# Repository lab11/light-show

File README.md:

Light Show
==========

This repository contains material to use one of the pseudo-addressable LED light
strips (based on the WS2801) with a Raspberry Pi.

Hardware
--------

In the hardware folder is a board design for a simple Raspberry Pi shield
that makes it easy to connect the lights to the RPi and an external power
supply.

Kernel Module
-------------

The kernel module is a simple driver for the lights that exports a character
device interface that an application can write to.

    make ARCH=arm CROSS_COMPILE=arm-linux-gnueabi-

C Code
------

The C code is a little bit of a hodgepodge of different applications that
run the lights with different applications.

    sudo apt-get install libjson0-dev

Remote Access
-------------

The app 'remote' in `c/apps/remote.c` provides network-controllable access for
the lights. Control of the strand is retained by the remote application for up
to 60 seconds, you may give up your quanta earlier by closing the connection. To
ensure responsiveness, a remote application must send a message every 3 seconds
or it will be dropped.

`remote/light_show.py` provides a basic python class and example for controlling
the lights over the remote interface.

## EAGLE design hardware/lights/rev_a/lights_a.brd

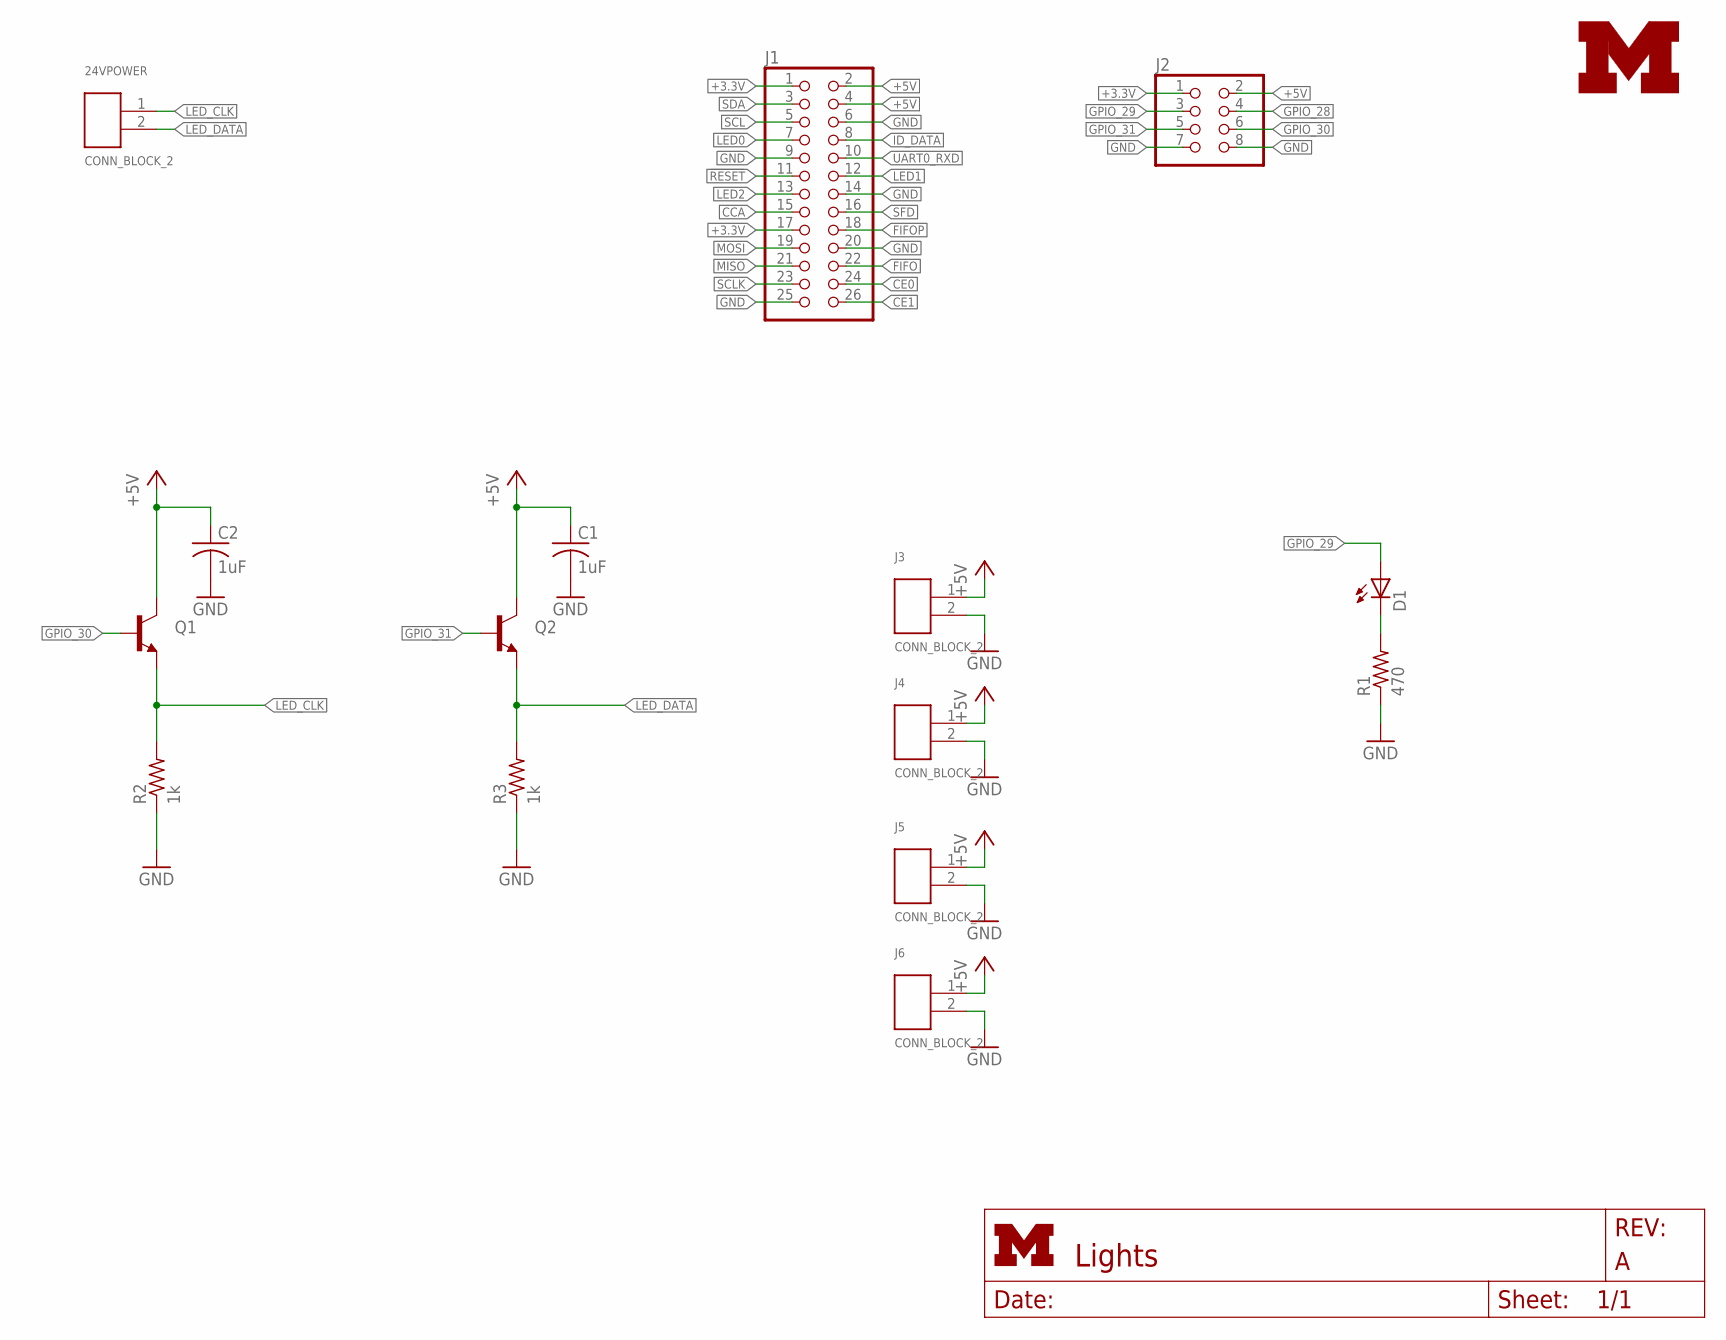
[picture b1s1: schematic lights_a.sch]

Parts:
24VPOWER: CONN_BLOCK_2
C1, C2: 1uF; C0603
D1: LED0603; LED-0603; DIGIKEY 160-1834-1-ND
J1: PINHD-2X13; 2X13; DIGIKEY SAM1204-13-ND
J2: PINHD-2X4; 2X04
J3, J4, J5, J6: CONN_BLOCK_2
Q1, Q2: TRANSISTOR_NPNSOT23; SOT23
R1: 470; R0603
R2, R3: 1k; R0603
U$1: UMICH_SOLID_SMALL; UMICH_SOLID_75MIL

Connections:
!RESET: J1.11
+3.3V: J1.1, J1.17, J2.1
+5V: C1.1, C2.1, J1.2, J1.4, J2.2, J3.1, J4.1, J5.1, J6.1, Q1.3 (C), Q2.3 (C)
CCA: J1.15
CE0: J1.24
CE1: J1.26
FIFO: J1.22
FIFOP: J1.18
GND: C1.2, C2.2, J1.6, J1.9, J1.14, J1.20, J1.25, J2.7, J2.8, J3.2, J4.2, J5.2, J6.2, R1.1, R2.1, R3.1
GPIO_28: J2.4
GPIO_29: D1.A, J2.3
GPIO_30: J2.6, Q1.1 (B)
GPIO_31: J2.5, Q2.1 (B)
ID_DATA: J1.8
LED0: J1.7
LED1: J1.12
LED2: J1.13
LED_CLK: 24VPOWER.1, Q1.2 (E), R2.2
LED_DATA: 24VPOWER.2, Q2.2 (E), R3.2
MISO: J1.21
MOSI: J1.19
unnamed: D1.C, R1.2
SCL: J1.5
SCLK: J1.23
SDA: J1.3
SFD: J1.16
UART0_RXD: J1.10

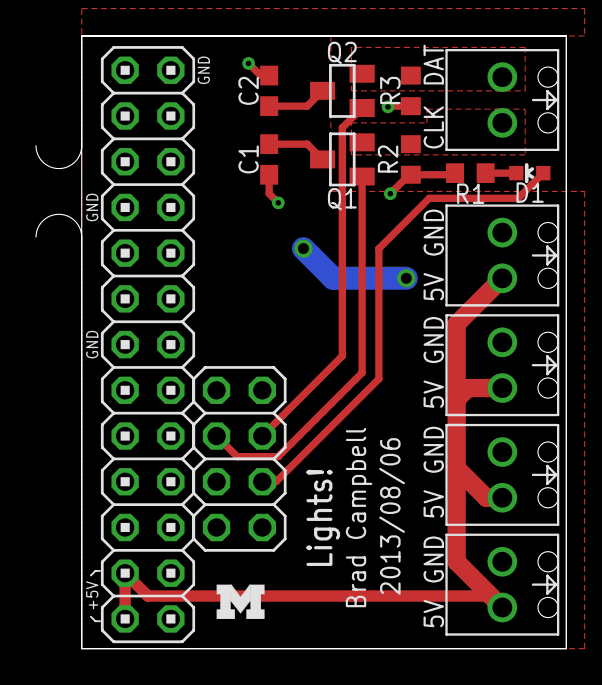
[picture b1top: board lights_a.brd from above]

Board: 2 copper layers, 29.5 x 34.0 mm, 16 parts (0 on the bottom side), 9 nets.

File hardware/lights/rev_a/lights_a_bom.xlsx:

Qty | Value | Device | Package | Parts | Description | DIGIKEY
2 | 1uF | C-USC0603 | C0603 | C1, C2 | CAPACITOR, American symbol
1 |  | LED0603 | LED-0603 | D1 | LEDs | 160-1834-1-ND
1 |  | PINHD-2X13 | 2X13 | J1 | PIN HEADER | SAM1204-13-ND
1 |  | PINHD-2X4 | 2X04 | J2 | PIN HEADER | SAM1204-04-ND
5 | CONN_BLOCK_2 | CONN_BLOCK_2 | CONN_BLOCK_2 | J3, J4, J5, J6 | 2x 0.100 in screw terminal block | 277-1273-ND
2 |  | TRANSISTOR_PFETSOT23 | SOT23 | Q1, Q2 | Transistor PFET | ZXMP2120FFCT-ND
1 | 470 | R-US_R0603 | R0603 | R1 | RESISTOR, American symbol
2 | 1k | R-US_R0603 | R0603 | R2, R3 | RESISTOR, American symbol

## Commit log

2013-06-29 First test pass on sparkfuns code
2013-06-29 gitignore
2013-06-29 random now walks down some colors
2013-06-29 new tracer app
2013-07-02 added stream receiver to tracer
    Need to check if it actually works yet/get the remaining code written.
    For now it just compiles.
2013-07-02 tracer app with door entry events
    Haven't tested on the lights, but it should work.
2013-07-03 bug fix, cross compiling
2013-07-04 kernel module
    Color updates are much better
2013-07-04 color fade works
2013-07-04 now selects user based on uniqname
    Can do different patterns.
2013-07-04 tracer run script - screen
2013-07-07 Updated tracer to new query settings
2013-07-08 Fixed profile id
2013-07-11 Updated tup - made lib directory
    Now compile objects for the lib files.
2013-07-11 added more effects
2013-07-12 debugging grow
2013-07-12 compile on rpi
2013-07-12 grow works now
    Slowed down blink.
2013-08-05 added simple app to do white
    Adds white leds slowly.
2013-08-14 updated led strip kernel module
    new timing
2013-08-16 better readme
2013-08-16 added hardware
2013-08-16 re-wrote the architecture
    Now each thing that wants to display on the lights is an app and can
    register itself with the main controller. Different apps will
    automatically cycle through.
2013-08-16 timing in whitebright
2013-08-16 forgot that select clears the timeout
    cause, you know, that's useful.
2013-08-17 changed how people can set their entry effect
2013-08-17 working on pong effect
2013-08-17 pong effect looks pretty good
2013-08-17 little slower
2013-08-17 added random app
2013-08-17 added some () that made app switching work
2013-08-17 added cube app
2013-08-20 tweaks to timing
2013-08-20 quicker tracer
2013-08-20 added coilcube app
    Had to move things around a touch to make it work.
2013-08-20 Updates to coilcube
2013-08-20 slowed down fast fade
2013-08-20 getting ready for pattup
2013-08-20 app gets called immediately
2013-08-20 added rpi debug target
2013-08-20 select timeout doesn't reset
2013-08-20 removed cc printf
2013-08-20 checks time limit now
    Also checks for select timeouts
2013-08-20 added time printout
2013-08-20 straightened out app timing
2013-09-06 Add a default variant
2013-09-06 Update to build debug with no rpi-nonsense
2013-09-07 Doin' it Brad-style. This works on my machine...
    and it will probably work on yours too! So long as you don't change
    the default path that json-c installs itself into. And really, who
    would do that anyway?
2013-09-07 Use constructors instead of cross-ref'd function calls
2013-09-07 Add remote control feature
2013-09-07 Ignore pyc's
2013-09-08 Add message types to remote app; add keepalive message
2013-09-09 Move some utilities to lights.h
2013-09-09 Add custom door entry for Pat
    This code is criminal, I know, but it makes pretty lights, so there.
2013-09-09 Update README to include remote interface
2013-10-02 Fix cube animation issue
    Committed untested and unbuilt on a plane with no WiFi, so... may
    not actually fix anything.
2013-10-02 Really fix cube animation
    Add missing stdbool header. Don't call updater when the app changes,
    instead let the app changed timeout skip mechanism execute the first
    call to the app.
2013-10-03 Added config for release on rpi
2013-10-03 removed all traces of bcm2835
2013-10-03 better apt-get install
2014-03-19 added a personalized lightshow for myself (Meghan)
2014-05-09 Throw an error if compiler isn't defined in tup
2014-12-17 Updating GATD URL to gatd.eecs

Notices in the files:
parts and their libraries:
SparkFun-LED: Licensing: CC v3.0 Share-Alike You are welcome to use this library for commercial purposes.
